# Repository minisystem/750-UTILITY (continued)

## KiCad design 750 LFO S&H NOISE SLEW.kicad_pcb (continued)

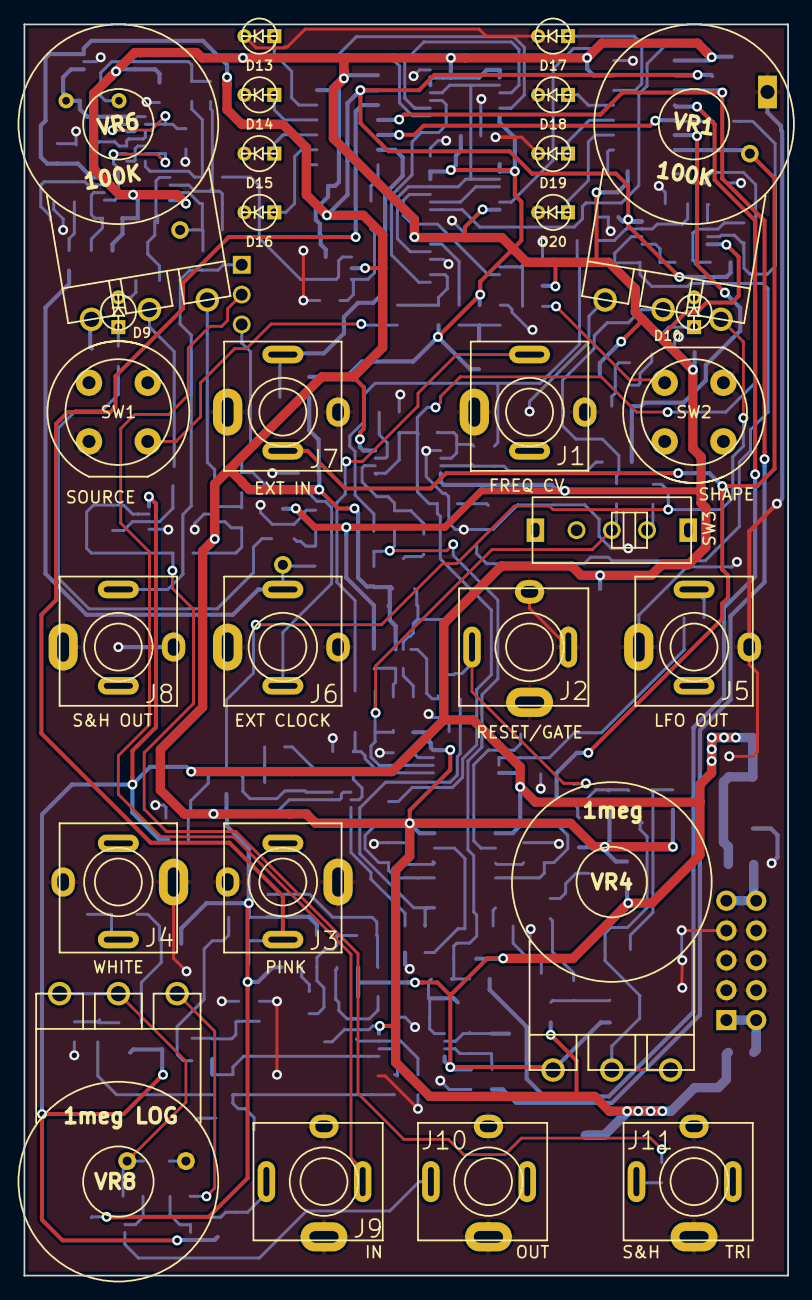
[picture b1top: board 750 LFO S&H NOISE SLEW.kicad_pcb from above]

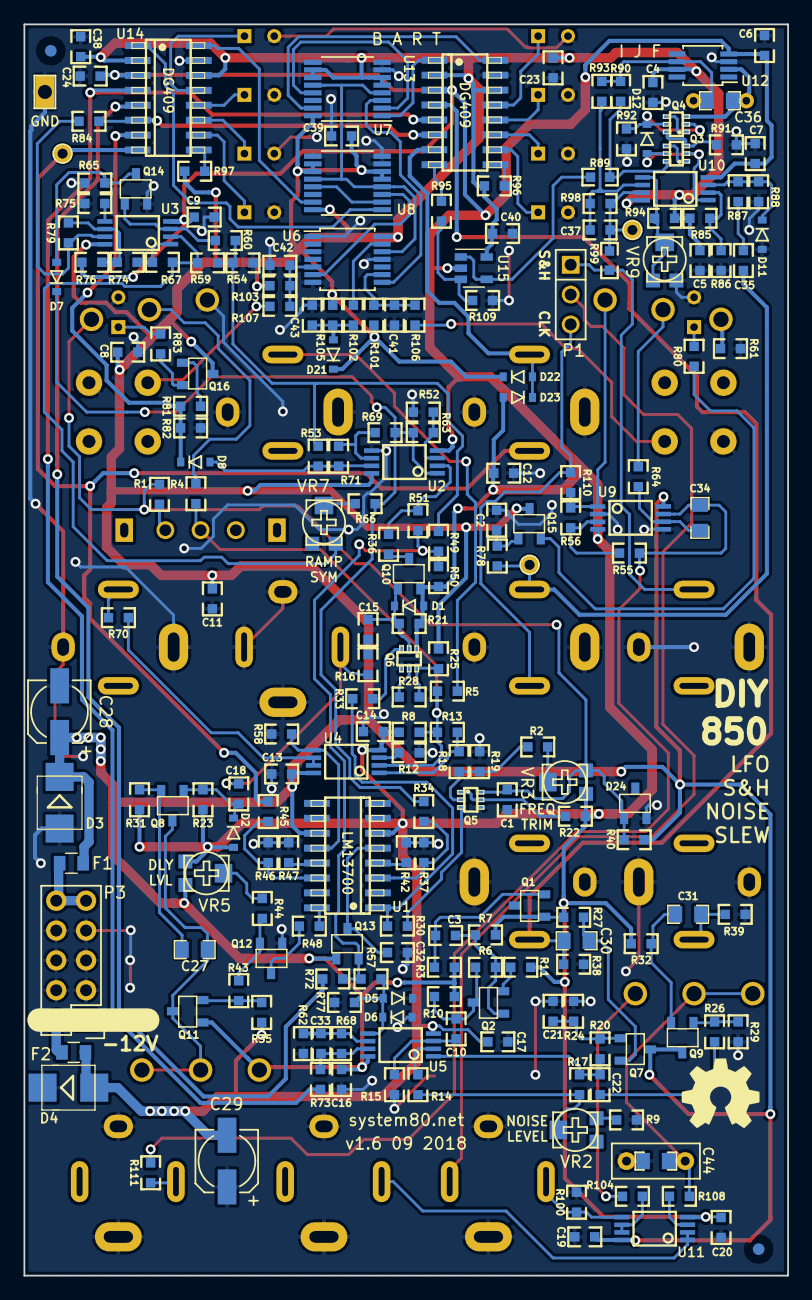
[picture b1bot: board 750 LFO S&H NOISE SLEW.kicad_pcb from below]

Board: 2 copper layers, 65.0 x 106.5 mm, 238 parts (210 on the bottom side), 145 nets.

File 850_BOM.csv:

"Id";"Designator";"Package";"Quantity";"Designation";"Supplier and ref";
1;"G***";"LOGO";1;"LOGO";;;
2;"R4,R1,R66";"SM0603-R-JRL";3;"180K";;;
3;"VR1,VR6";"RV16A-41-JRL";2;"100K";;;
4;"J2,J3,J1,J4,J6,J8,J9,J10,J11";"PJ-301B-JACK-SLOTS";9;"PJ301BM";;;
5;"Q6,Q5";"SOT363-JRL";2;"MBT3946DW";;;
6;"Q4,Q3";"SOT363-JRL";2;"2N7002";;;
7;"U6";"TSSOP-14_4.4x5mm_Pitch0.65mm";1;"CD40106";;;
8;"C3,C15,C18,C32";"SM0603-C-JRL";4;"100n";;;
9;"C4,C5,C6,C7,C8,C9,C11,C12,C13,C14,C16,C17,C19,C20,C23,C24,C38,C39,C40,C1";"SM0603-C-JRL";20;"0.1µ";;;
10;"C10";"SM0603-C-JRL";1;"33n";;;
11;"C21";"SM0603-C-JRL";1;"10n";;;
12;"C22,C35,C37,C2";"SM0603-C-JRL";4;"1n";;;
13;"C33";"SM0603-C-JRL";1;"47n";;;
14;"C36";"SM0603-C-JRL";1;"0.01μ";;;
15;"C41,C42";"SM0603-C-JRL";2;"0.47μ";;;
16;"C43";"SM0603-C-JRL";1;"1μ";;;
17;"D1,D2,D5,D6,D7,D8,D11,D12,D22,D23";"SOD323-JRL";10;"1N4148";;;
18;"D3,D4";"SMB-1C2A";2;"S1BB";;;
19;"D9,D10,D13,D14,D15,D16,D17,D18,D19,D20";"3MM-LED-C1A2";10;"LED";;;
20;"D21";"SOD323-C1A2";1;"1N4148";;;
21;"J5,J7";"PJ-301B-JACK-SLOTS";2;"JACK_MONO_SW";;;
22;"P3";"Pin_Header_Straight_2x05";1;"CONN_02X05";;;
23;"Q1,Q2,Q7,Q8,Q9,Q10,Q15,Q16";"SOT23-132-JRL";8;"MMBT3904";;;
24;"Q11,Q13,Q14";"SOT23-JRL";3;"J112";;;
25;"Q12";"SOT23-132-JRL";1;"MMBT3906";;;
26;"R2";"SM0603-R-JRL";1;"820K";;;
27;"R3,R6";"SM0603-R-JRL";2;"1.5meg";;;
28;"R5,R7,R21,R22,R23,R24,R29,R52,R60,R65,R68,R69,R74,R79,R82,R85,R98,R105,R109";"SM0603-R-JRL";19;"100K";;;
29;"R8,R94";"SM0603-R-JRL";2;"120K";;;
30;"R9";"SM0603-R-JRL";1;"8.2K";;;
31;"R10,R55,R72,R76";"SM0603-R-JRL";4;"150K";;;
32;"R11";"SM0603-R-JRL";1;"2.2K";;;
33;"R12,R13,R16,R20,R26,R27,R28,R32,R33,R36,R50,R62,R86,R108";"SM0603-R-JRL";14;"10K";;;
34;"R14,R15,R45,R56";"SM0603-R-JRL";4;"330K";;;
35;"R17";"SM0603-R-JRL";1;"680K";;;
36;"R18,R31";"SM0603-R-JRL";2;"4.7K";;;
37;"R19,R37,R42,R46,R47,R64,R70,R73,R80,R83,R84,R87,R99,R110,R111,R40";"SM0603-R-JRL";16;"1K";;;
38;"R25,R30,R48,R95";"SM0603-R-JRL";4;"22K";;;
39;"R34,R59";"SM0603-R-JRL";2;"15K";;;
40;"R35,R51,R101,R103,R77";"SM0603-R-JRL";5;"33K";;;
41;"R38,R39,R53,R57,R58,R63,R75,R78,R81,R93";"SM0603-R-JRL";10;"47K";;;
42;"R43,R44,R67";"SM0603-R-JRL";3;"39K";;;
43;"R49,R71";"SM0603-R-JRL";2;"82K";;;
44;"R54";"SM0603-R-JRL";1;"56K";;;
45;"R61,R104";"SM0603-R-JRL";2;"100";;;
46;"R88";"SM0603-R-JRL";1;"20K";;;
47;"R89,R90";"SM0603-R-JRL";2;"470";;;
48;"R91,R100";"SM0603-R-JRL";2;"1meg";;;
49;"R92";"SM0603-R-JRL";1;"18K";;;
50;"R96,R97";"SM0603-R-JRL";2;"3.3K";;;
51;"R102,R106,R107";"SM0603-R-JRL";3;"330";;;
52;"SW1,SW2";"KS-01Q-02-JRL";2;"KS-01Q";;;
53;"TP3";"TEST_POINT_LOOP_4592";1;"CONN_1";;;
54;"U1";"SO16-JRL";1;"LM13700";;;
55;"U7,U8";"TSSOP-16_4.4x5mm_Pitch0.65mm";2;"CD4027";;;
56;"U12";"MSOP-8_3x3mm_Pitch0.65mm";1;"MAX9945";;;
57;"U13,U14";"SO16-JRL";2;"DG409";;;
58;"C30,C31";"SM0805-HAND";2;"10μ";;;
59;"C44";"CAP-5MM-BOX-0805-COMBO";1;"470n";;;
60;"C34,C27";"SM0805-HAND";2;"4.7μ";;;
61;"VR4";"RV16A-41-JRL";1;"1meg";;;
62;"VR8";"RV16A-41-JRL";1;"1meg LOG";;;
63;"U11,U10,U9,U5,U4,U2,U3";"TSSOP8-JRL";7;"TL072-";;;
64;"C28,C29";"c_elec_5x5.3";2;"10μF";;;
65;"TP7,TP8,TP6";"TEST_POINT_SMALL";3;"CONN_1";;;
66;"VR2,VR9";"TC33X-2";2;"10K";;;
67;"VR3,VR5,VR7";"TC33X-2";3;"100K";;;
68;"P1";"PIN_ARRAY_3X1";1;"CONN_01X03";;;
69;"REF***";"OSHW-Symbol_6.7x6mm_SilkScreen";1;"OSHW-Symbol_6.7x6mm_SilkScreen";;;
70;"U15";"SOT-23-5";1;"TS321";;;
71;"SW3";"SS-12F108-1P2T-SLIDE";1;"SPDT";;;
72;"REF**,REF**";"fiducial-1mm";2;"fiducial-1mm";;;
73;"D24";"SOT23-132-JRL";1;"LM4040-10";;;
74;"F1,F2";"C_0805";2;"PTC 0.1A";;;

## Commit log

2016-03-13 working on 150 LFO
2016-03-14 schematic more or less captured. Still need to check and also confirm noise circuit
2016-03-14 tidy up a bit. Could start part assignment and rough layout now
2016-03-16 noise source done. removed redundant power-on-reset circuit
2016-03-17 tidy up. next step: annotate
2016-03-17 put PNP and NPN in LFO expo converter into single 3946 package, little bit of clean up
2016-03-17 added filtered rails for noise circuit a la TR-808
2016-03-18 annotated, footprints assinged, netlist generated
2016-03-18 started placing comps on PCB. jacks, pots and LEDs placed
2016-03-18 more component placement
2016-04-09 placing components, starting a bit from scratch
2016-04-10 placing and routing. so slow...
2016-04-11 almost done placing LFO, then on to S&H
2016-04-11 LFO all placed, partially routed
2016-04-12 everything placed but some test points and all decoupling caps
2016-04-12 routing power
2016-04-13 routing power and ground, all components placed
2016-04-14 stitching ground plane
2016-04-14 routed
2016-04-16 tidy up
2016-05-27 adjust silkscreen
2016-12-09 added notes to schematic based on building first prototype
2016-12-10 working on panel
2016-12-11 update schematic with changes for next version, still need to be implemented in pcb
2016-12-11 import panel graphics hole centres into pcbnew
2016-12-12 routing changes to pcb
2016-12-13 almost done routing second version, 3 ground signals left to stitch
2016-12-13 update test point footprint, adjust silkscreen
2016-12-18 silkscreen tweaking. getting ready to generate gerbers and order v1.1 PCBs
2016-12-18 added buffer to s&h input
2016-12-21 ordered
2017-01-08 fixed a few reference positions
2017-03-20 fixed range switch pin swap. started moving top layer bypass cpas to bottom layer. still need to fix delay or slew pot pin mixup - can't remember which one is mixed up
2017-03-20 moved all smt to bottom layer, swapped VR4 delay time pot pins
2017-03-20 silkscreen tweaked, ready for panel check
2017-03-21 finished panel mechanical layer
2017-03-21 checked and ready to order PCB
2017-03-22 ordered PCBs, created dimensioned panel drawing for machinist
2017-04-21 working on v1.3. almost done
2017-04-29 added a couple of superflurous output protection resistors
2017-05-02 changed R25 value to improve LFO reset response
2017-05-02 generated v1.3 gerbers for ordering
2017-05-24 notes
2017-05-25 commit before adding voltage referencd for LFO
2017-05-26 LFO voltage reference added and routed"
    l
    q
    ;ksadjf
    q
    exit
    "
2017-05-26 tweak
2017-05-27 tweakings
2017-05-29 850 gerbers plotted
2017-06-23 export BOM
2017-08-06 started working on manual, added BOM
2017-09-04 working on manual
2017-09-05 manual almost done
2017-09-06 more manual shennanigans
2018-03-11 commit with updated PCB graphics, about to change 0603 footprints via text edit of pcb file
2018-03-14 last commit before changing 0603 footprints
2018-03-18 panelization with updated 0603 footprints done
2018-03-20 panelized, sent for fabrication
2018-09-20 updated manual, .pos, bom
2018-09-20 removed System80 logos
